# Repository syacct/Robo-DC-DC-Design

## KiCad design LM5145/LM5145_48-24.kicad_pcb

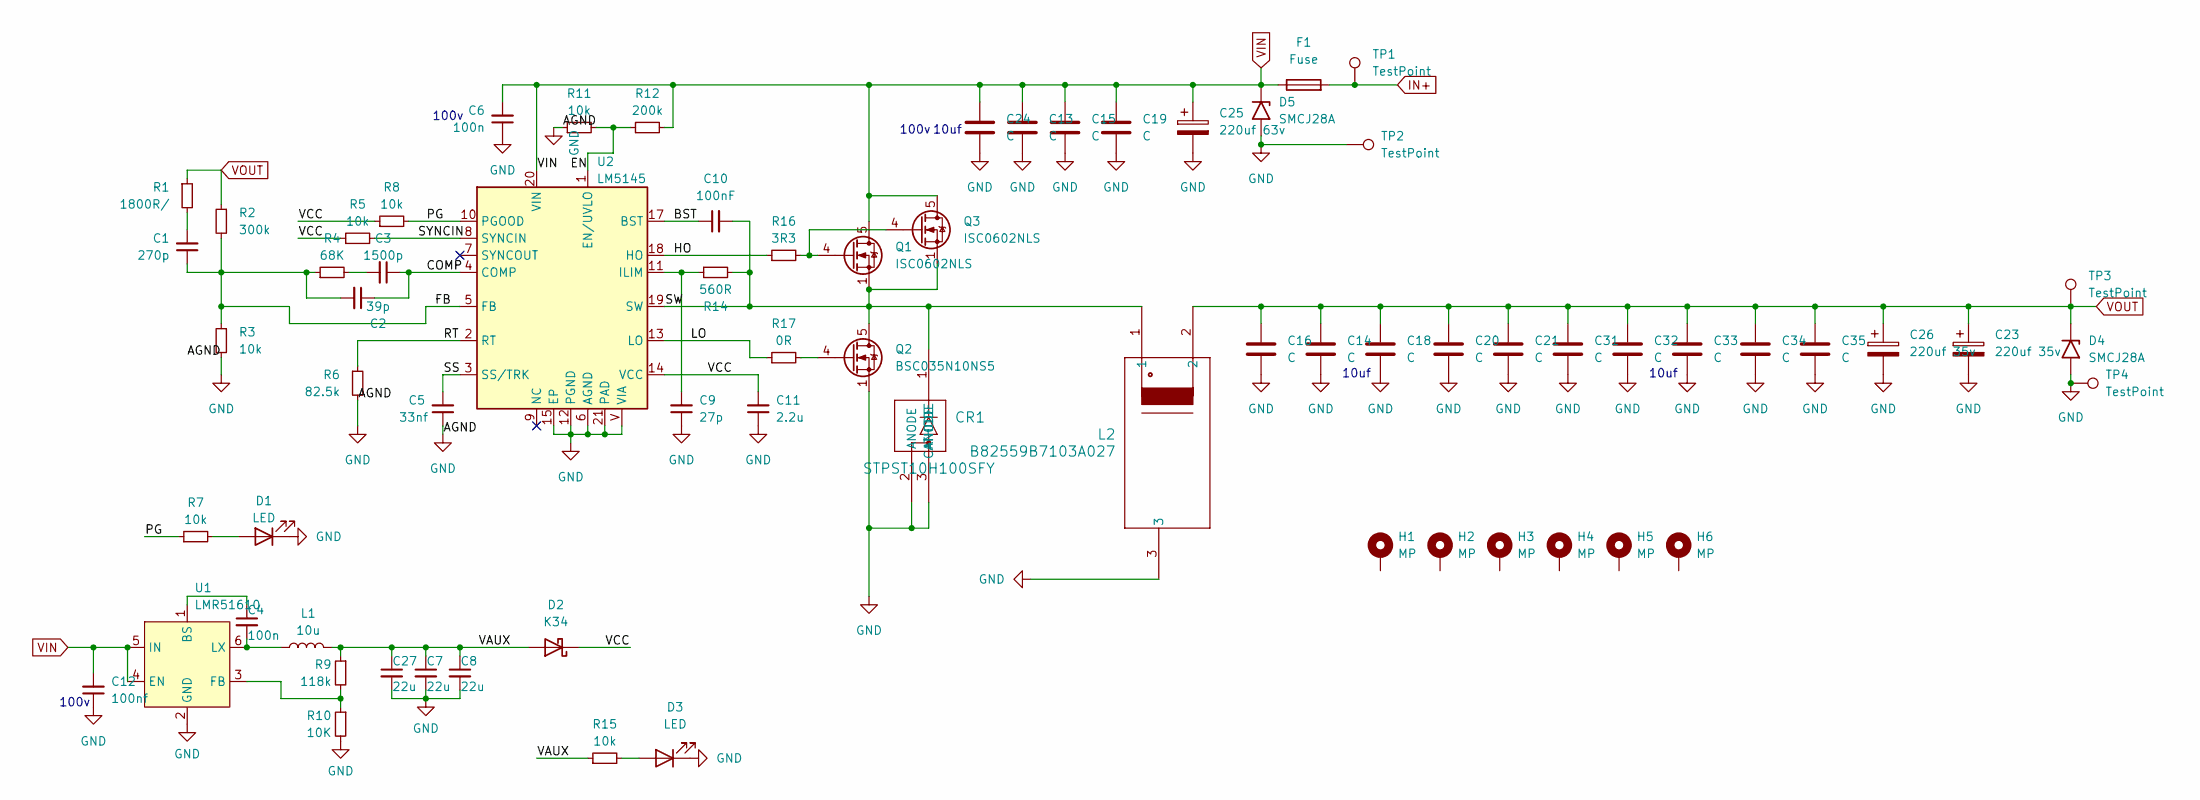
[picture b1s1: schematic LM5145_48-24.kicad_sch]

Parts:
C1: 270p; C_0603_1608Metric
C2: 39p; C_0603_1608Metric
C3: 1500p; C_0603_1608Metric
C4, C6: 100n; C_0603_1608Metric
C5: 33nf; C_0603_1608Metric
C7, C8, C27: 22u; C_0805_2012Metric
C9: 27p; C_0603_1608Metric
C10: 100nF; C_0603_1608Metric
C11: 2.2u; C_0603_1608Metric
C12: 100nf; C_0603_1608Metric
C13, C15, C19, C24: C; C_1210_3225Metric
C14, C16, C18, C20, C21, C31, C32, C33, C34, C35: C; C_1206_3216Metric
C23, C26: 220uf 35v; CP_Elec_8x10.5
C25: 220uf 63v; CP_Elec_8x10.5
CR1: STPST10H100SFY; PSMCTO-277A_STM
D1, D3: LED; LED_0603_1608Metric
D2: K34; D_SMF
D4, D5: SMCJ28A; D_SMC
F1: Fuse; Fuse_Littelfuse-NANO2-451_453
H1, H2, H3, H4, H5, H6: MP; MountingHole_2.7mm_M2.5_DIN965_Pad
L1: 10u; L_Sunlord_MWSA0402S
L2: B82559B7103A027; L_PR27XX
Q1, Q3: ISC0602NLS; TDSON-8-1
Q2: BSC035N10NS5; TDSON-8-1
R1: 1800R/; R_0603_1608Metric
R2: 300k; R_0603_1608Metric
R3, R5, R7, R8, R11, R15: 10k; R_0603_1608Metric
R4: 68K; R_0603_1608Metric
R6: 82.5k; R_0603_1608Metric
R9: 118k; R_0603_1608Metric
R10: 10K; R_0603_1608Metric
R12: 200k; R_0603_1608Metric
R14: 560R; R_0603_1608Metric
R16: 3R3; R_0603_1608Metric
R17: 0R; R_0603_1608Metric
TP1, TP2, TP3, TP4: TestPoint; TestPoint_Pad_3.0x3.0mm
U1: LMR51610; SOT-23-6
U2: LM5145; RGY0020B

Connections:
/BST: C10.1, U2.17 (BST)
/COMP: C2.1, C3.1, U2.4 (COMP)
/EN: R11.2, R12.1, U2.1 (EN/UVLO)
/FB: C1.1, C2.2, R2.2, R3.1, R4.1, U2.5 (FB)
/HO: R16.1, U2.18 (HO)
/LO: R17.1, U2.13 (LO)
/PG: R7.1, R8.2, U2.10 (PGOOD)
/RT: R6.1, U2.2 (RT)
/SS: C5.2, U2.3 (SS/TRK)
/SW: C10.2, CR1.1 (CATHODE), L2.1, Q1.1 (S), Q1.2 (S), Q1.3 (S), Q2.5 (D), Q3.1 (S), Q3.2 (S), Q3.3 (S), R14.2, U2.19 (SW)
/SYNCIN: R5.2, U2.8 (SYNCIN)
/VAUX: C7.1, C8.1, C27.1, D2.2 (A), L1.2, R9.1, R15.1
/VCC: C11.2, D2.1 (K), R5.1, R8.1, U2.14 (VCC)
GND: C5.1, C6.1, C7.2, C8.2, C9.1, C11.1, C12.1, C13.2, C14.2, C15.2, C16.2, C18.2, C19.2, C20.2, C21.2, C23.2, C24.2, C25.2, C26.2, C27.2, C31.2, C32.2, C33.2, C34.2, C35.2, CR1.2 (ANODE), CR1.3 (ANODE), D1.1 (K), D3.1 (K), D4.2 (A2), D5.2 (A2), L2.3, Q2.1 (S), Q2.2 (S), Q2.3 (S), R3.2, R6.2, R10.2, R11.1, TP2.1, TP4.1, U1.2 (GND), U2.6 (AGND), U2.12 (PGND), U2.15 (EP), U2.21 (PAD), U2.V (VIA)
IN+: F1.2, TP1.1
unnamed: C1.2, R1.2
unnamed: C3.2, R4.2
unnamed: D1.2 (A), R7.2
unnamed: D3.2 (A), R15.2
unnamed: Q1.4 (G), Q3.4 (G), R16.2
unnamed: Q2.4 (G), R17.2
unnamed: C4.1, U1.1 (BS)
unnamed: R9.2, R10.1, U1.3 (FB)
unnamed: C4.2, L1.1, U1.6 (LX)
unnamed: C9.2, R14.1, U2.11 (ILIM)
VIN: C6.2, C12.2, C13.1, C15.1, C19.1, C24.1, C25.1, D5.1 (A1), F1.1, Q1.5 (D), Q3.5 (D), R12.2, U1.4 (EN), U1.5 (IN), U2.20 (VIN)
VOUT: C14.1, C16.1, C18.1, C20.1, C21.1, C23.1, C26.1, C31.1, C32.1, C33.1, C34.1, C35.1, D4.1 (A1), L2.2, R1.1, R2.1, TP3.1

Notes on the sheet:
100v
10uf

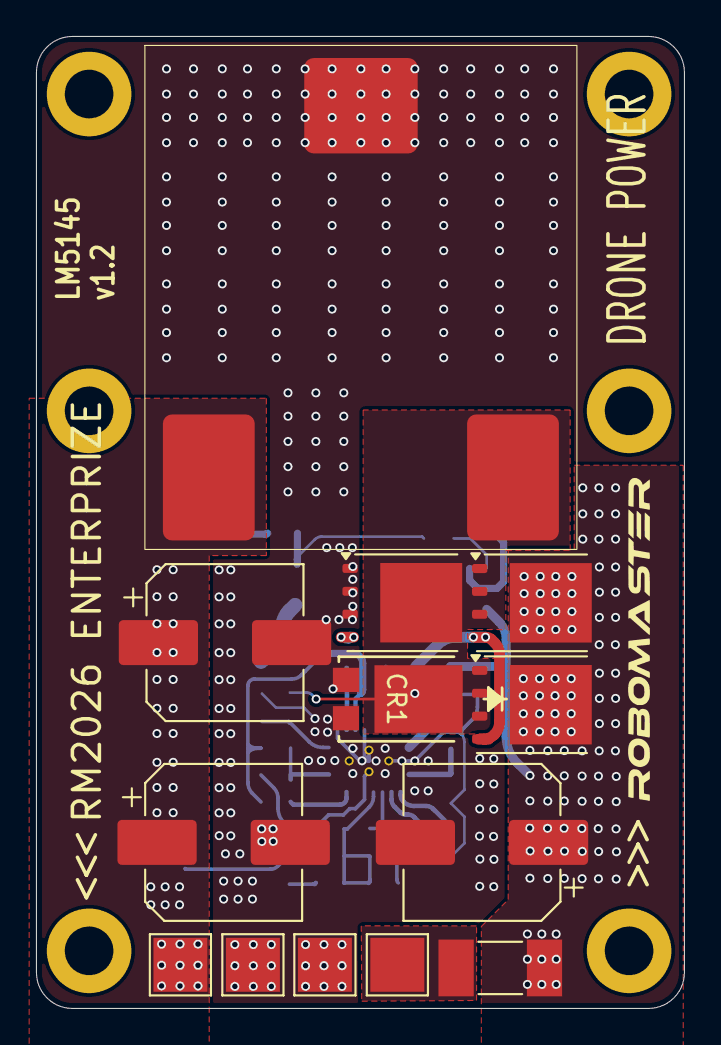
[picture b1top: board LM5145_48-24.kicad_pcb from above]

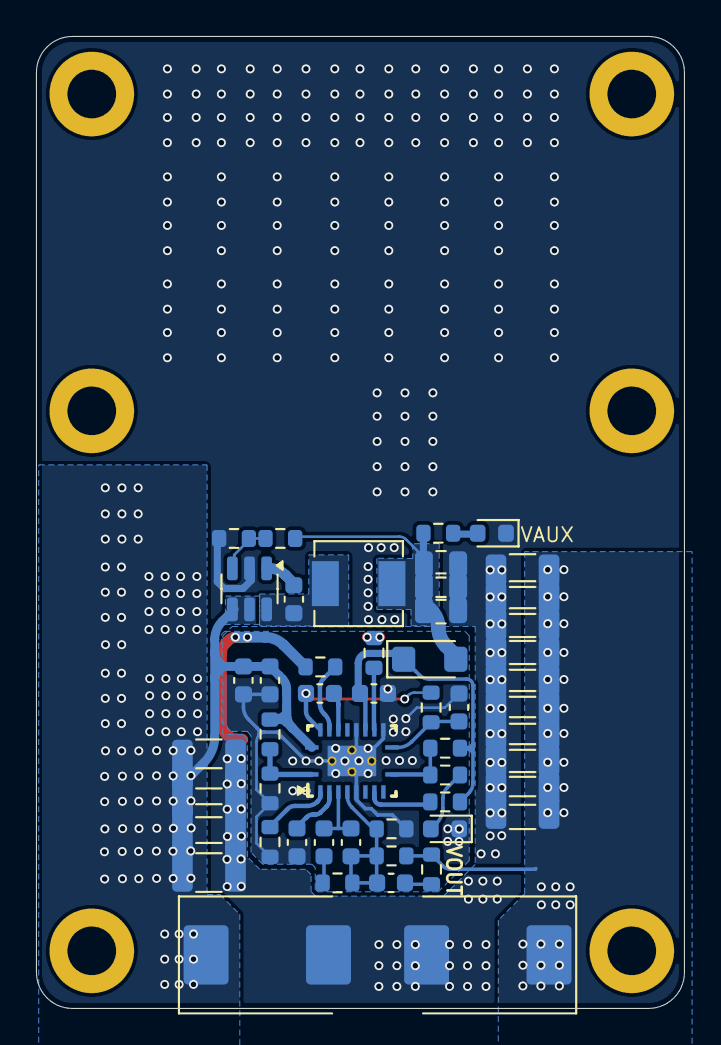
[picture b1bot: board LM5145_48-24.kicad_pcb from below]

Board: 2 copper layers, 36.0 x 54.0 mm, 70 parts (51 on the bottom side), 27 nets.

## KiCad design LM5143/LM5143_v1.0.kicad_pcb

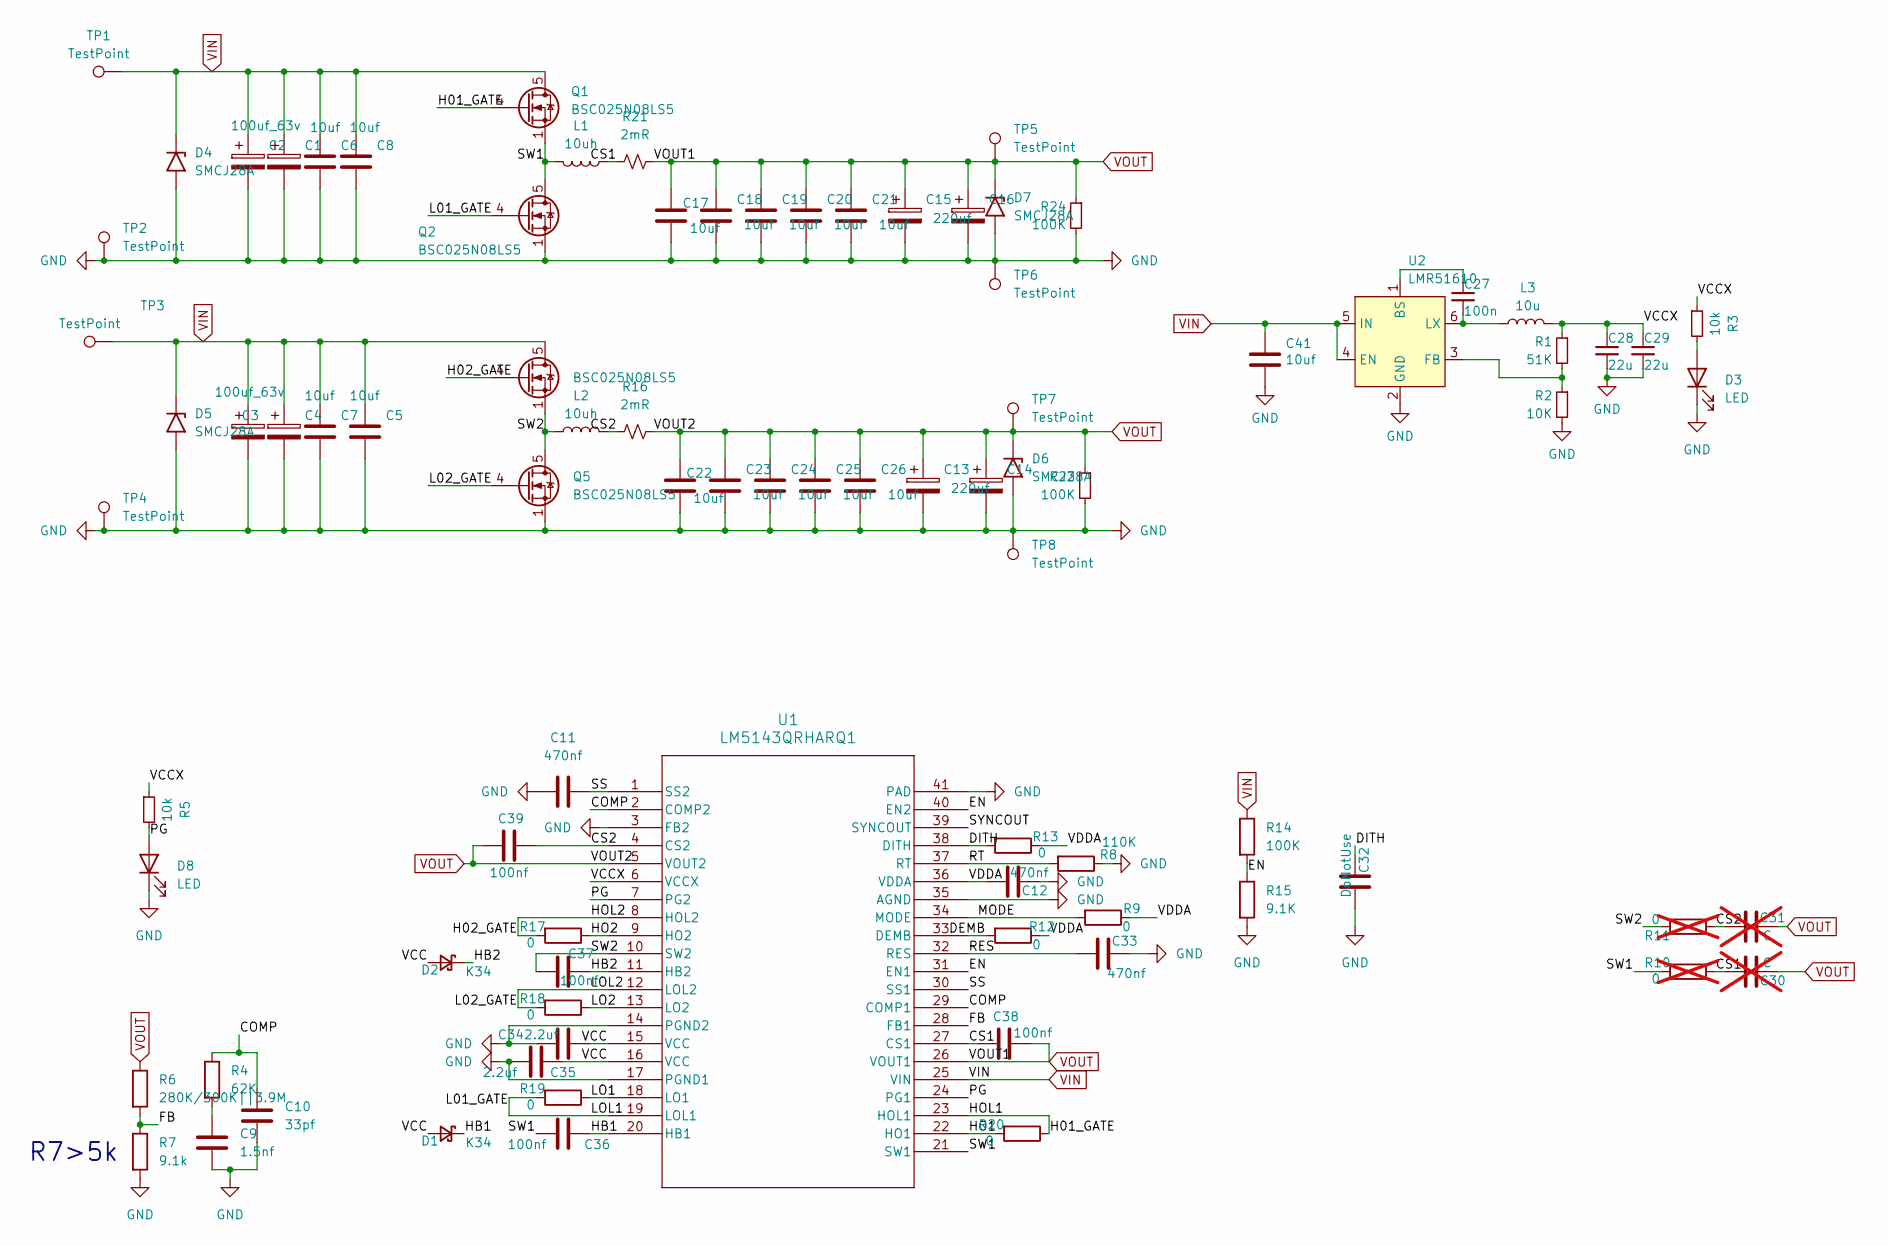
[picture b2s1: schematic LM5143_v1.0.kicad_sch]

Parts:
C1, C2, C3: 100uf_63v; CP_Radial_D8.0mm_P3.50mm
C4: 100uf_63V; CP_Radial_D8.0mm_P3.50mm
C5, C6, C7, C8: 10uf; C_1210_3225Metric
C9: 1.5nf; C_0603_1608Metric
C10: 33pf; C_0603_1608Metric
C11, C12, C33: 470nf; C_0603_1608Metric
C13, C14, C15, C16: 220uf; CP_Radial_D8.0mm_P3.50mm
C17, C18, C19, C20, C21, C22, C23, C24, C25, C26, C41: 10uf; C_1206_3216Metric
C27: 100n; C_0603_1608Metric
C28, C29: 22u; C_0805_2012Metric
C30, C31: C; C_0603_1608Metric; not fitted
C32: DoNotUse; C_0603_1608Metric
C34, C35: 2.2uf; C_0603_1608Metric
C36, C37, C38, C39: 100nf; C_0603_1608Metric
D1, D2: K34; D_SOD-323_HandSoldering
D3, D8: LED; LED_0603_1608Metric
D4, D5, D6, D7: SMCJ28A; D_SMA
L1, L2: 10uh; PQ20__
L3: 10u; L_Sunlord_MWSA0402S
Q1, Q2, Q4, Q5: BSC025N08LS5; TDSON-8-1
R1: 51K; R_0603_1608Metric
R2: 10K; R_0603_1608Metric
R3, R5: 10k; R_0603_1608Metric
R4: 62K; R_0603_1608Metric
R6: 280K/300K||3.9M; R_0603_1608Metric
R7: 9.1k; R_0603_1608Metric
R8: 110K; R_0603_1608Metric
R9, R12, R13, R17, R18, R19, R20: 0; R_0603_1608Metric
R10, R11: 0; R_0603_1608Metric; not fitted
R14, R23, R24: 100K; R_0603_1608Metric
R15: 9.1K; R_0603_1608Metric
R16, R21: 2mR; R_2512_6332Metric
TP1, TP2, TP3, TP4, TP5, TP6, TP7, TP8: TestPoint; TestPoint_Pad_3.0x3.0mm
U1: LM5143QRHARQ1; VQFN40_RHA_TEX
U2: LMR51610; SOT-23-6

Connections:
/COMP: C10.1, R4.1, U1.2 (COMP2), U1.29 (COMP1)
/CS1: C30.2, C38.1, L1.1, R10.1, R21.1, U1.27 (CS1)
/CS2: C31.2, C39.2, L2.2, R11.1, R16.1, U1.4 (CS2)
/DEMB: R12.2, U1.33 (DEMB)
/DITH: C32.1, R13.2, U1.38 (DITH)
/EN: R14.2, R15.1, U1.31 (EN1), U1.40 (EN2)
/FB: R6.2, R7.1, U1.28 (FB1)
/H01_GATE: Q1.4 (G), R20.1, U1.23 (HOL1)
/H02_GATE: Q4.4 (G), R17.2, U1.8 (HOL2)
/HB1: C36.1, D1.1 (K), U1.20 (HB1)
/HB2: C37.2, D2.1 (K), U1.11 (HB2)
/HO1: R20.2, U1.22 (HO1)
/HO2: R17.1, U1.9 (HO2)
/L01_GATE: Q2.4 (G), R19.2, U1.19 (LOL1)
/L02_GATE: Q5.4 (G), R18.2, U1.12 (LOL2)
/LO1: R19.1, U1.18 (LO1)
/LO2: R18.1, U1.13 (LO2)
/MODE: R9.2, U1.34 (MODE)
/PG: D8.2 (A), R5.2, U1.7 (PG2), U1.24 (PG1)
/RES: C33.1, U1.32 (RES)
/RT: R8.2, U1.37 (RT)
/SS: C11.1, U1.1 (SS2), U1.30 (SS1)
/SW1: C36.2, L1.2, Q1.1 (S), Q1.2 (S), Q1.3 (S), Q2.5 (D), R10.2, U1.21 (SW1)
/SW2: C37.1, L2.1, Q4.1 (S), Q4.2 (S), Q4.3 (S), Q5.5 (D), R11.2, U1.10 (SW2)
/SYNCOUT: U1.39 (SYNCOUT)
/VCC: C34.1, C35.1, D1.2 (A), D2.2 (A), U1.15 (VCC), U1.16 (VCC)
/VCCX: C28.1, C29.1, L3.2, R1.1, R3.1, R5.1, U1.6 (VCCX)
/VDDA: C12.2, R9.1, R12.1, R13.1, U1.36 (VDDA)
GND: C1.2, C2.2, C3.2, C4.2, C5.2, C6.2, C7.2, C8.2, C9.2, C10.2, C11.2, C12.1, C13.2, C14.2, C15.2, C16.2, C17.2, C18.2, C19.2, C20.2, C21.2, C22.2, C23.2, C24.2, C25.2, C26.2, C28.2, C29.2, C32.2, C33.2, C34.2, C35.2, C41.2, D3.1 (K), D4.2 (A2), D5.2 (A2), D6.2 (A2), D7.2 (A2), D8.1 (K), Q2.1 (S), Q2.2 (S), Q2.3 (S), Q5.1 (S), Q5.2 (S), Q5.3 (S), R2.2, R7.2, R8.1, R15.2, R23.2, R24.2, TP2.1, TP4.1, TP6.1, TP8.1, U1.3 (FB2), U1.14 (PGND2), U1.17 (PGND1), U1.35 (AGND), U1.41 (PAD), U2.2 (GND)
unnamed: C9.1, R4.2
unnamed: D3.2 (A), R3.2
unnamed: C27.1, U2.1 (BS)
unnamed: R1.2, R2.1, U2.3 (FB)
unnamed: C27.2, L3.1, U2.6 (LX)
VIN: C1.1, C2.1, C3.1, C4.1, C5.1, C6.1, C7.1, C8.1, C41.1, D4.1 (A1), D5.1 (A1), Q1.5 (D), Q4.5 (D), R14.1, TP1.1, TP3.1, U1.25 (VIN), U2.4 (EN), U2.5 (IN)
VOUT: C13.1, C14.1, C15.1, C16.1, C17.1, C18.1, C19.1, C20.1, C21.1, C22.1, C23.1, C24.1, C25.1, C26.1, C30.1, C31.1, C38.2, C39.1, D6.1 (A1), D7.1 (A1), R6.1, R16.2, R21.2, R23.1, R24.1, TP5.1, TP7.1, U1.5 (VOUT2), U1.26 (VOUT1)

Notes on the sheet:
R7>5k

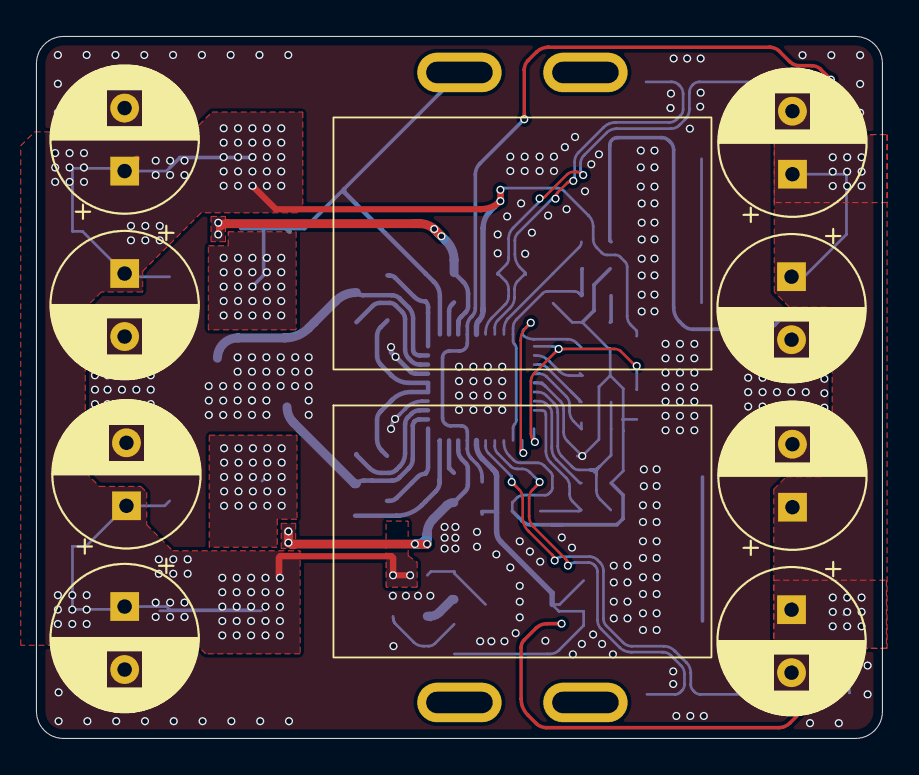
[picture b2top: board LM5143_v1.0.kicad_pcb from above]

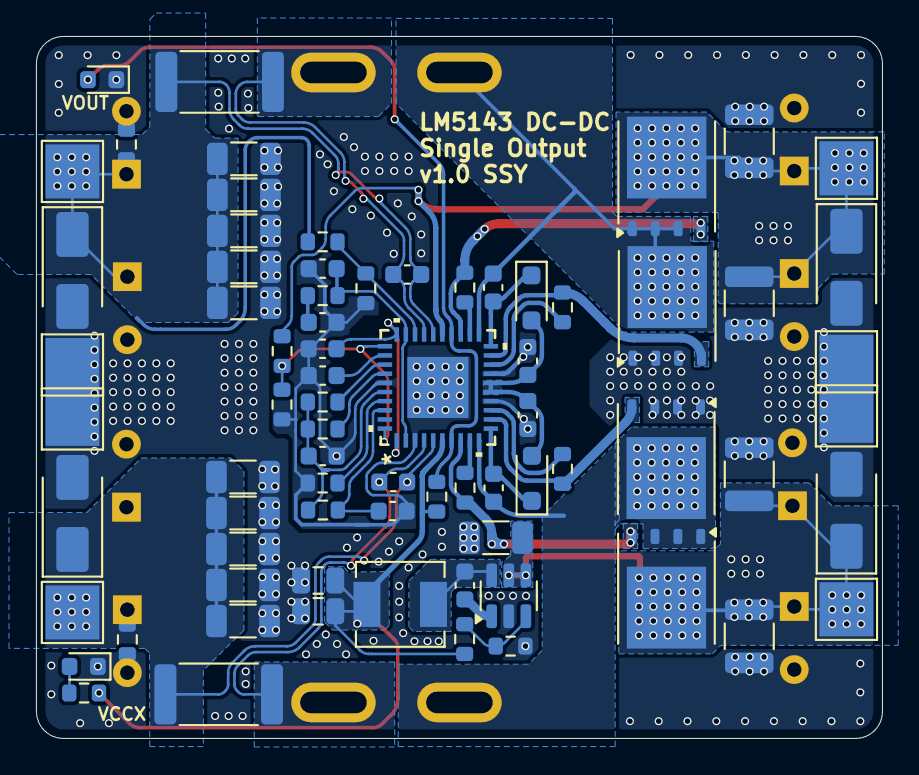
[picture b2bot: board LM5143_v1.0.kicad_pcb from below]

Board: 2 copper layers, 47.0 x 39.0 mm, 84 parts (74 on the bottom side), 35 nets.

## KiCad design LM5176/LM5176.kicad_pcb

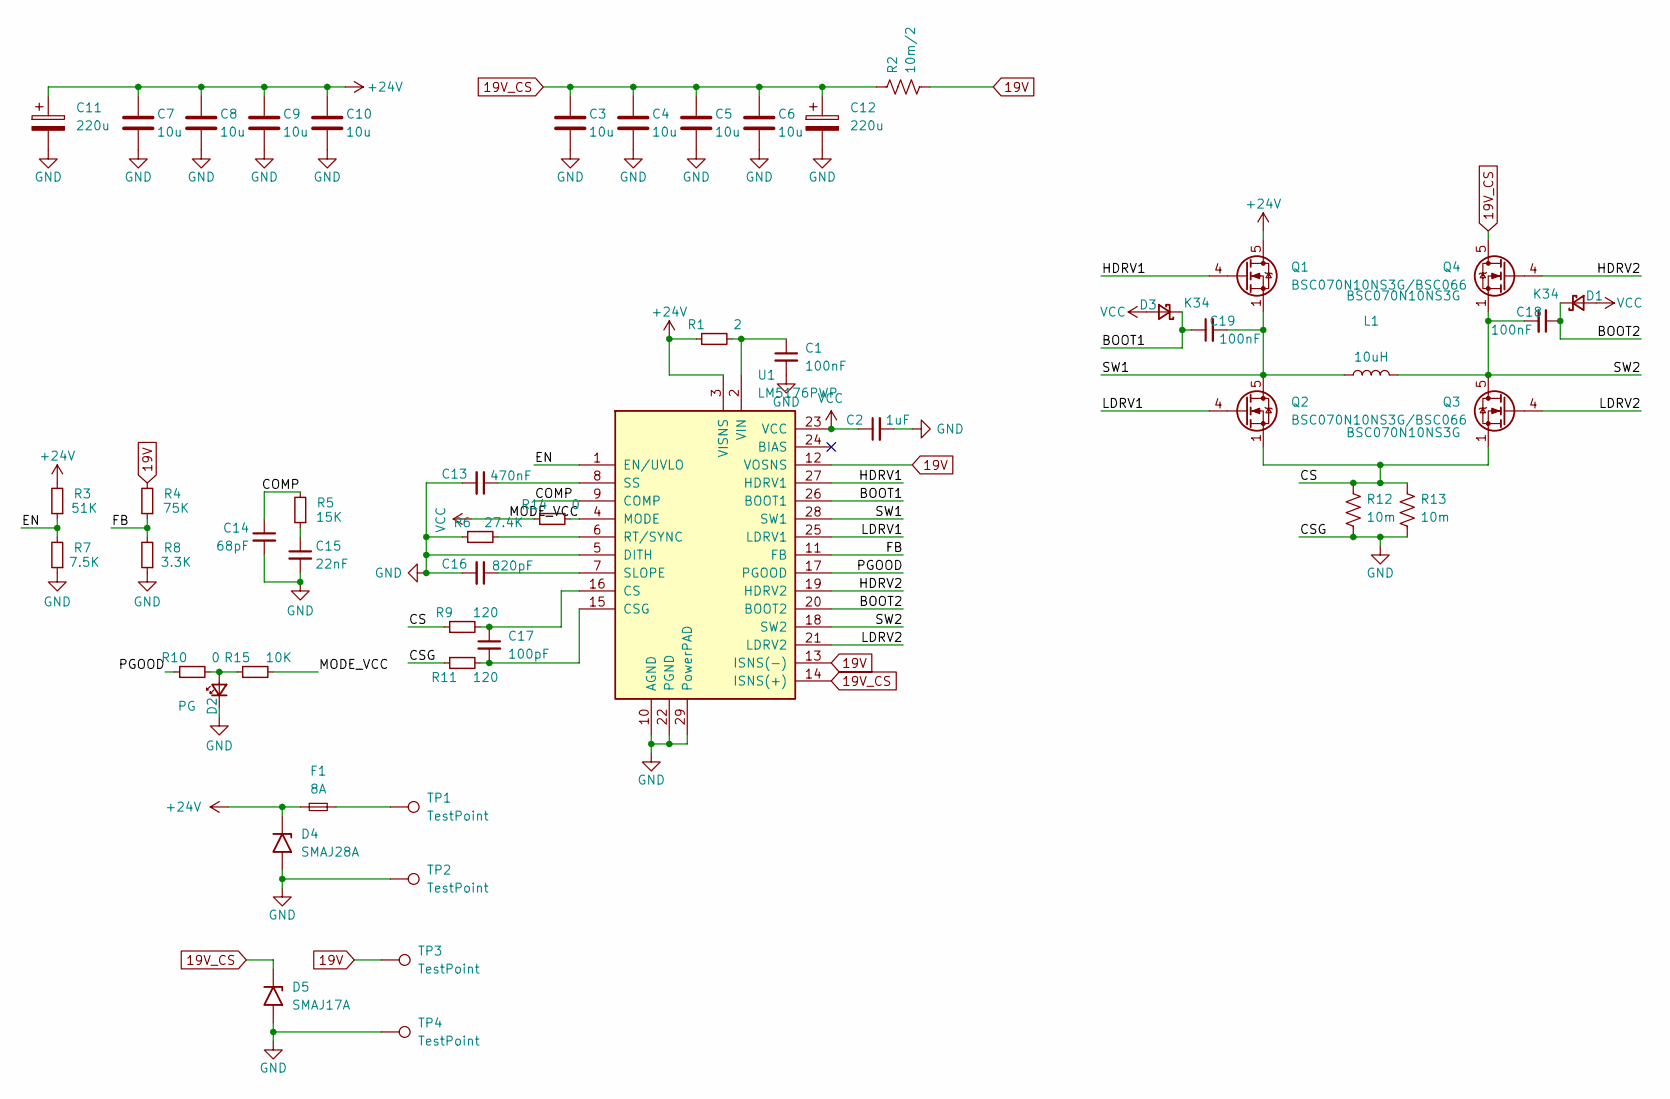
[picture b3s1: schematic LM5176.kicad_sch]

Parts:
C1, C18, C19: 100nF; C_0603_1608Metric
C2: 1uF; C_0603_1608Metric
C3, C4, C5, C6, C7, C8, C9, C10: 10u; C_1206_3216Metric
C11: 220u; C_D8xH12mm_Hor
C12: 220u; C_D8xH12mm_Hor_Flip
C13: 470nF; C_0603_1608Metric
C14: 68pF; C_0603_1608Metric
C15: 22nF; C_0603_1608Metric
C16: 820pF; C_0603_1608Metric
C17: 100pF; C_0603_1608Metric
D1, D3: K34; D_SOD-323_HandSoldering
D2: PG; LED_0603_1608Metric
D4: SMAJ28A; D_SMA
D5: SMAJ17A; D_SMA
F1: 8A; Fuse_1206_3216Metric
L1: 10uH; L_Bourns_SRP1770TA_16.9x16.9mm
Q1, Q2: BSC070N10NS3G/BSC066; TDSON-8-1
Q3, Q4: BSC070N10NS3G; TDSON-8-1
R1: 2; R_0603_1608Metric
R2: 10m/2; R_1206_3216Metric
R3: 51K; R_0603_1608Metric
R4: 75K; R_0603_1608Metric
R5: 15K; R_0603_1608Metric
R6: 27.4K; R_0603_1608Metric
R7: 7.5K; R_0603_1608Metric
R8: 3.3K; R_0603_1608Metric
R9, R11: 120; R_0603_1608Metric
R10, R14: 0; R_0603_1608Metric
R12, R13: 10m; R_1206_3216Metric
R15: 10K; R_0603_1608Metric
TP1, TP2, TP3, TP4: TestPoint; TestPoint_Pad_3.0x3.0mm
U1: LM5176PWP; HTSSOP-28-1EP_4.4x9.7mm_P0.65mm_EP3.4x9.5mm_ThermalVias

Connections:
19V: R2.2, R4.2, TP3.1, U1.12 (VOSNS), U1.13 (ISNS(-))
19V_CS: C3.1, C4.1, C5.1, C6.1, C12.1, D5.1 (A1), Q4.5 (D), R2.1, U1.14 (ISNS(+))
+24V: C7.1, C8.1, C9.1, C10.1, C11.1, D4.1 (A1), F1.1, Q1.5 (D), R1.1, R3.2, U1.3 (VISNS)
/BOOT1: C19.1, D3.1 (K), U1.26 (BOOT1)
/BOOT2: C18.1, D1.1 (K), U1.20 (BOOT2)
/COMP: C14.1, R5.2, U1.9 (COMP)
/CS: Q2.1 (S), Q2.2 (S), Q2.3 (S), Q3.1 (S), Q3.2 (S), Q3.3 (S), R9.1, R12.1, R13.1
/EN: R3.1, R7.2, U1.1 (EN/UVLO)
/FB: R4.1, R8.2, U1.11 (FB)
/HDRV1: Q1.4 (G), U1.27 (HDRV1)
/HDRV2: Q4.4 (G), U1.19 (HDRV2)
/LDRV1: Q2.4 (G), U1.25 (LDRV1)
/LDRV2: Q3.4 (G), U1.21 (LDRV2)
/MODE_VCC: R14.2, R15.2, U1.4 (MODE)
/PGOOD: R10.1, U1.17 (PGOOD)
/SW1: C19.2, L1.1, Q1.1 (S), Q1.2 (S), Q1.3 (S), Q2.5 (D), U1.28 (SW1)
/SW2: C18.2, L1.2, Q3.5 (D), Q4.1 (S), Q4.2 (S), Q4.3 (S), U1.18 (SW2)
GND: C1.2, C2.2, C3.2, C4.2, C5.2, C6.2, C7.2, C8.2, C9.2, C10.2, C11.2, C12.2, C13.2, C14.2, C15.2, C16.2, D2.1 (K), D4.2 (A2), D5.2 (A2), R6.1, R7.1, R8.1, R11.1, R12.2, R13.2, TP2.1, TP4.1, U1.5 (DITH), U1.10 (AGND), U1.22 (PGND), U1.29 (PowerPAD)
unnamed: C15.1, R5.1
unnamed: D2.2 (A), R10.2, R15.1
unnamed: F1.2, TP1.1
unnamed: C17.1, R9.2, U1.16 (CS)
unnamed: C17.2, R11.2, U1.15 (CSG)
unnamed: R6.2, U1.6 (RT/SYNC)
unnamed: C16.1, U1.7 (SLOPE)
unnamed: C13.1, U1.8 (SS)
unnamed: C1.1, R1.2, U1.2 (VIN)
VCC: C2.1, D1.2 (A), D3.2 (A), R14.1, U1.23 (VCC)

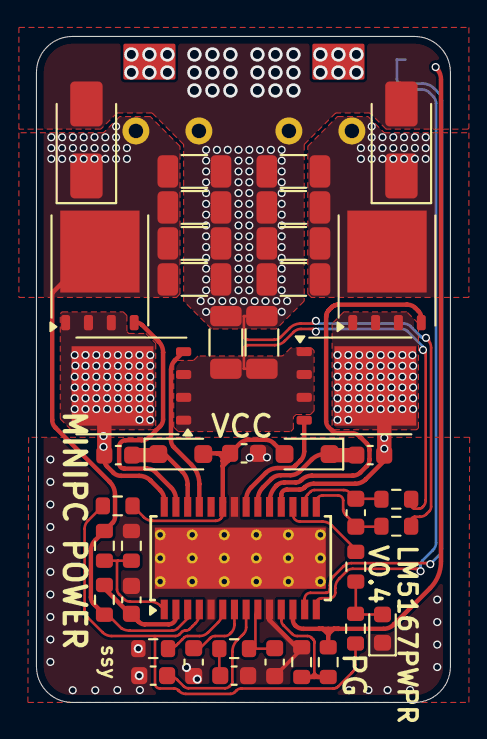
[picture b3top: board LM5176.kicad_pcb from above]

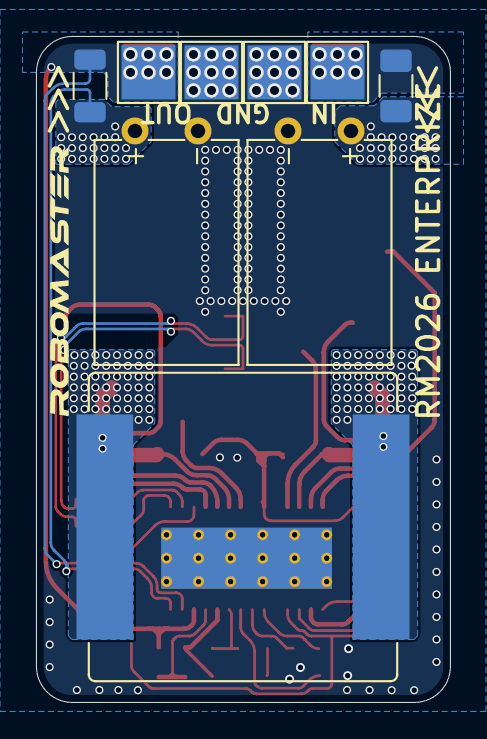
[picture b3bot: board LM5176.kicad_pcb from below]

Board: 2 copper layers, 23.0 x 37.0 mm, 50 parts (9 on the bottom side), 28 nets.
